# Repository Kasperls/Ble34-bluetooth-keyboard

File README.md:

# Ble34-bluetooth-keyboard
Files from the Ble34 project

Custom PCB for a wireless keyboard using running ZMK on nRF52840.

Flashed using picoprobe as debugger.

The final keyboard has a slick case in mate black and can be used both wired and not.

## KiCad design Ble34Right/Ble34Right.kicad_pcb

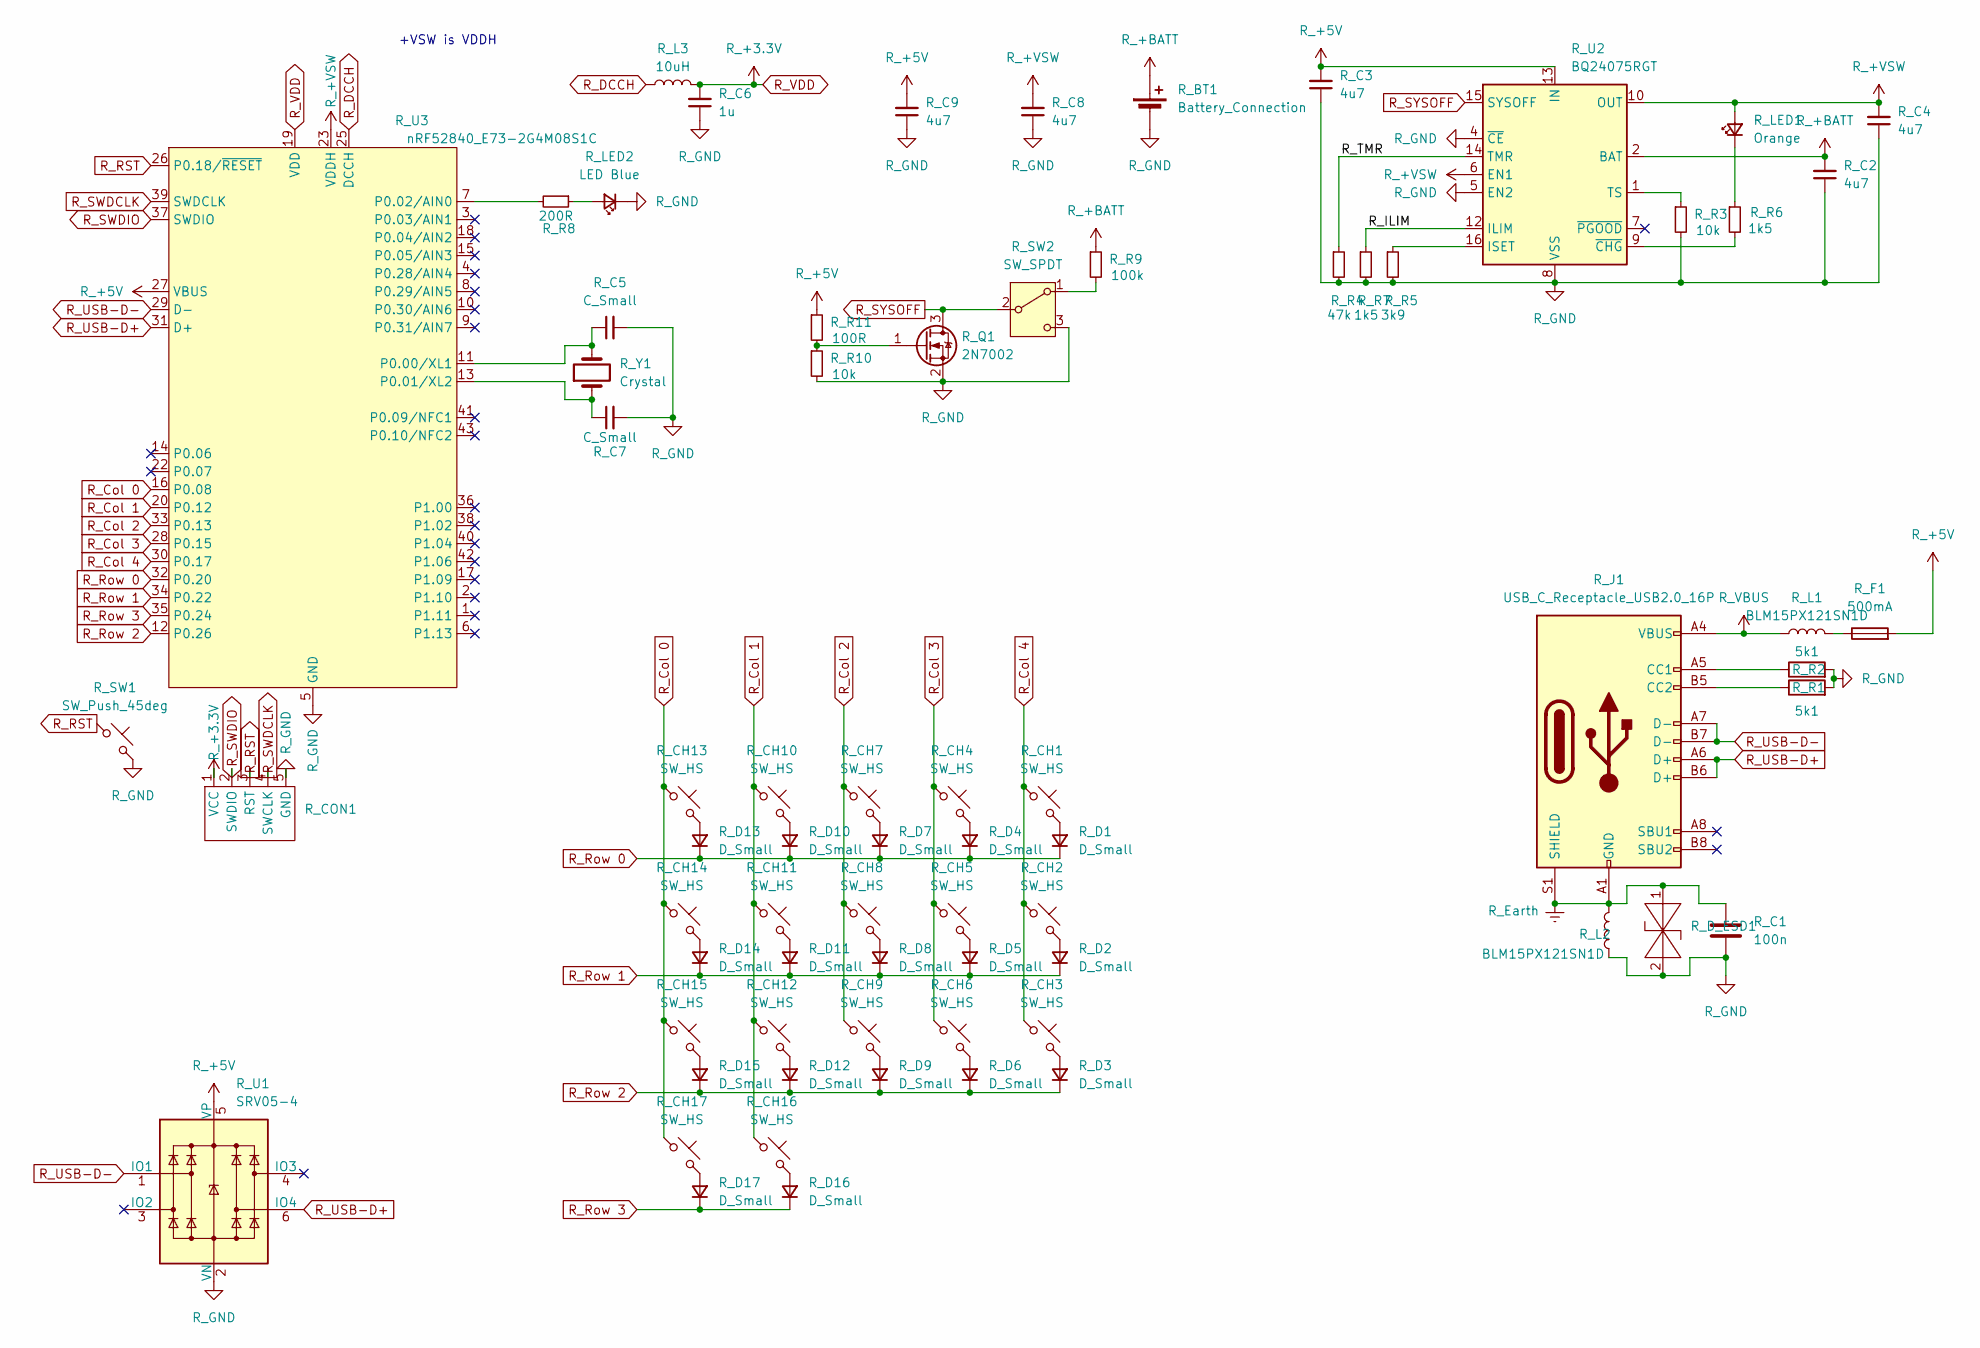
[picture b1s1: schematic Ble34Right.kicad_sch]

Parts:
R_BT1: Battery_Connection; Battery_Connector
R_C1: 100n; C_0603_1608Metric; LCSC C14663
R_C2, R_C3, R_C4, R_C8, R_C9: 4u7; C_0603_1608Metric; LCSC C1669
R_C5, R_C7: C_Small; C_0603_1608Metric; LCSC C38523
R_C6: 1u; C_0603_1608Metric; LCSC C115062
R_CH1, R_CH2, R_CH3, R_CH4, R_CH5, R_CH6, R_CH7, R_CH8, R_CH9, R_CH10, R_CH11, R_CH12, R_CH13, R_CH14, R_CH15, R_CH16, R_CH17: SW_HS; SW_choc_v1_HS_CPG135001S30_1u
R_CON1: SWD_CONNECTION
R_D1, R_D2, R_D3, R_D4, R_D5, R_D6, R_D7, R_D8, R_D9, R_D10, R_D11, R_D12, R_D13, R_D14, R_D15, R_D16, R_D17: D_Small; D_SOD-123; LCSC C2972760
R_D_ESD1: BSD3C051V; LCSC C151996
R_F1: 500mA; Fuse_0603_1608Metric; LCSC C910820
R_J1: USB_C_Receptacle_USB2.0_16P; USB_C_Receptacle_HRO_TYPE-C-31-M-14
R_L1, R_L2: BLM15PX121SN1D; R_0402_1005Metric; LCSC C88970
R_L3: 10uH; Fuse_0603_1608Metric; LCSC C1035
R_LED1: Orange; LED_0603_1608Metric; LCSC C2286
R_LED2: LED Blue; LED_0603_1608Metric; LCSC C2288
R_Q1: 2N7002; SOT-23; LCSC C332103
R_R1, R_R2: 5k1; R_0603_1608Metric; LCSC C23186
R_R3, R_R10: 10k; R_0603_1608Metric; LCSC C2930027
R_R4: 47k; R_0603_1608Metric; LCSC C2907042
R_R5: 3k9; R_0603_1608Metric; LCSC C2924132
R_R6, R_R7: 1k5; R_0603_1608Metric; LCSC C22843
R_R8: 200R; R_0603_1608Metric; LCSC C8218
R_R9: 100k; R_0603_1608Metric; LCSC C14675
R_R11: 100R; R_0603_1608Metric; LCSC C22775
R_SW1: SW_Push_45deg; TS-1088-SW; LCSC C720477
R_SW2: SW_SPDT; SW_MSK12C02-HB; LCSC C963206
R_U1: SRV05-4; SOT-23-6; LCSC C558418
R_U2: BQ24075RGT; VQFN-16-1EP_3x3mm_P0.5mm_EP1.6x1.6mm; LCSC C2865459
R_U3: nRF52840_E73-2G4M08S1C; LCSC C356849
R_Y1: Crystal; Crystal_SMD_3215-2Pin_3.2x1.5mm; LCSC C97606

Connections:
/R_ILIM: R_R7.1, R_U2.12 (ILIM)
/R_TMR: R_R4.1, R_U2.14 (TMR)
unnamed: R_CH13.2, R_D13.2 (A)
unnamed: R_CH10.2, R_D10.2 (A)
unnamed: R_CH7.2, R_D7.2 (A)
unnamed: R_CH4.2, R_D4.2 (A)
unnamed: R_CH1.2, R_D1.2 (A)
unnamed: R_CH14.2, R_D14.2 (A)
unnamed: R_CH11.2, R_D11.2 (A)
unnamed: R_CH8.2, R_D8.2 (A)
unnamed: R_CH5.2, R_D5.2 (A)
unnamed: R_CH2.2, R_D2.2 (A)
unnamed: R_CH15.2, R_D15.2 (A)
unnamed: R_CH12.2, R_D12.2 (A)
unnamed: R_CH9.2, R_D9.2 (A)
unnamed: R_CH6.2, R_D6.2 (A)
unnamed: R_CH3.2, R_D3.2 (A)
unnamed: R_CH17.2, R_D17.2 (A)
unnamed: R_CH16.2, R_D16.2 (A)
unnamed: R_F1.1, R_L1.2
unnamed: R_J1.A5 (CC1), R_R2.1
unnamed: R_J1.B5 (CC2), R_R1.1
unnamed: R_LED1.1 (K), R_R6.1
unnamed: R_LED2.2 (A), R_R8.1
unnamed: R_Q1.1 (G), R_R10.1, R_R11.2
unnamed: R_R9.2, R_SW2.1 (A)
unnamed: R_C5.1, R_U3.11 (P0.00/XL1), R_Y1.2
unnamed: R_C7.1, R_U3.13 (P0.01/XL2), R_Y1.1
unnamed: R_R8.2, R_U3.7 (P0.02/AIN0)
unnamed: R_R5.1, R_U2.16 (ISET)
unnamed: R_R3.1, R_U2.1 (TS)
unnamed: R_R6.2, R_U2.9 (~CHG)
R_+5V: R_C3.2, R_C9.2, R_F1.2, R_R11.1, R_U1.5 (VP), R_U2.13 (IN), R_U3.27 (VBUS)
R_+BATT: R_BT1.1 (+), R_C2.2, R_R9.1, R_U2.2 (BAT), R_U2.3 (BAT)
R_+VSW: R_C4.2, R_C8.2, R_LED1.2 (A), R_U2.6 (EN1), R_U2.10 (OUT), R_U2.11 (OUT), R_U3.23 (VDDH)
R_Col 0: R_CH13.1, R_CH14.1, R_CH15.1, R_CH17.1, R_U3.16 (P0.08)
R_Col 1: R_CH10.1, R_CH11.1, R_CH12.1, R_CH16.1, R_U3.20 (P0.12)
R_Col 2: R_CH7.1, R_CH8.1, R_CH9.1, R_U3.33 (P0.13)
R_Col 3: R_CH4.1, R_CH5.1, R_CH6.1, R_U3.28 (P0.15)
R_Col 4: R_CH1.1, R_CH2.1, R_CH3.1, R_U3.30 (P0.17)
R_DCCH: R_L3.1, R_U3.25 (DCCH)
R_Earth: R_C1.1, R_D_ESD1.1, R_J1.A1 (GND), R_J1.A12 (GND), R_J1.B1 (GND), R_J1.B12 (GND), R_J1.S1 (SHIELD), R_L2.2
R_GND: R_BT1.2 (-), R_C1.2, R_C2.1, R_C3.1, R_C4.1, R_C5.2, R_C6.1, R_C7.2, R_C8.1, R_C9.1, R_CON1.5 (GND), R_D_ESD1.2, R_L2.1, R_LED2.1 (K), R_Q1.2 (S), R_R1.2, R_R2.2, R_R3.2, R_R4.2, R_R5.2, R_R7.2, R_R10.2, R_SW1.2, R_SW2.3 (C), R_U1.2 (VN), R_U2.4 (~CE), R_U2.5 (EN2), R_U2.8 (VSS), R_U2.17 (VSS), R_U3.5 (GND), R_U3.21 (GND), R_U3.24 (GND)
R_RST: R_CON1.3 (RST), R_SW1.1, R_U3.26 (P0.18/~RESET)
R_Row 0: R_D1.1 (K), R_D4.1 (K), R_D7.1 (K), R_D10.1 (K), R_D13.1 (K), R_U3.32 (P0.20)
R_Row 1: R_D2.1 (K), R_D5.1 (K), R_D8.1 (K), R_D11.1 (K), R_D14.1 (K), R_U3.34 (P0.22)
R_Row 2: R_D3.1 (K), R_D6.1 (K), R_D9.1 (K), R_D12.1 (K), R_D15.1 (K), R_U3.12 (P0.26)
R_Row 3: R_D16.1 (K), R_D17.1 (K), R_U3.35 (P0.24)
R_SWDCLK: R_CON1.4 (SWCLK), R_U3.39 (SWDCLK)
R_SWDIO: R_CON1.2 (SWDIO), R_U3.37 (SWDIO)
R_SYSOFF: R_Q1.3 (D), R_SW2.2 (B), R_U2.15 (SYSOFF)
R_USB-D+: R_J1.A6 (D+), R_J1.B6 (D+), R_U1.6 (IO4), R_U3.31 (D+)
R_USB-D-: R_J1.A7 (D-), R_J1.B7 (D-), R_U1.1 (IO1), R_U3.29 (D-)
R_VBUS: R_J1.A4 (VBUS), R_J1.A9 (VBUS), R_J1.B4 (VBUS), R_J1.B9 (VBUS), R_L1.1
R_VDD: R_C6.2, R_CON1.1 (VCC), R_L3.2, R_U3.19 (VDD)

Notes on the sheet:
+VSW is VDDH

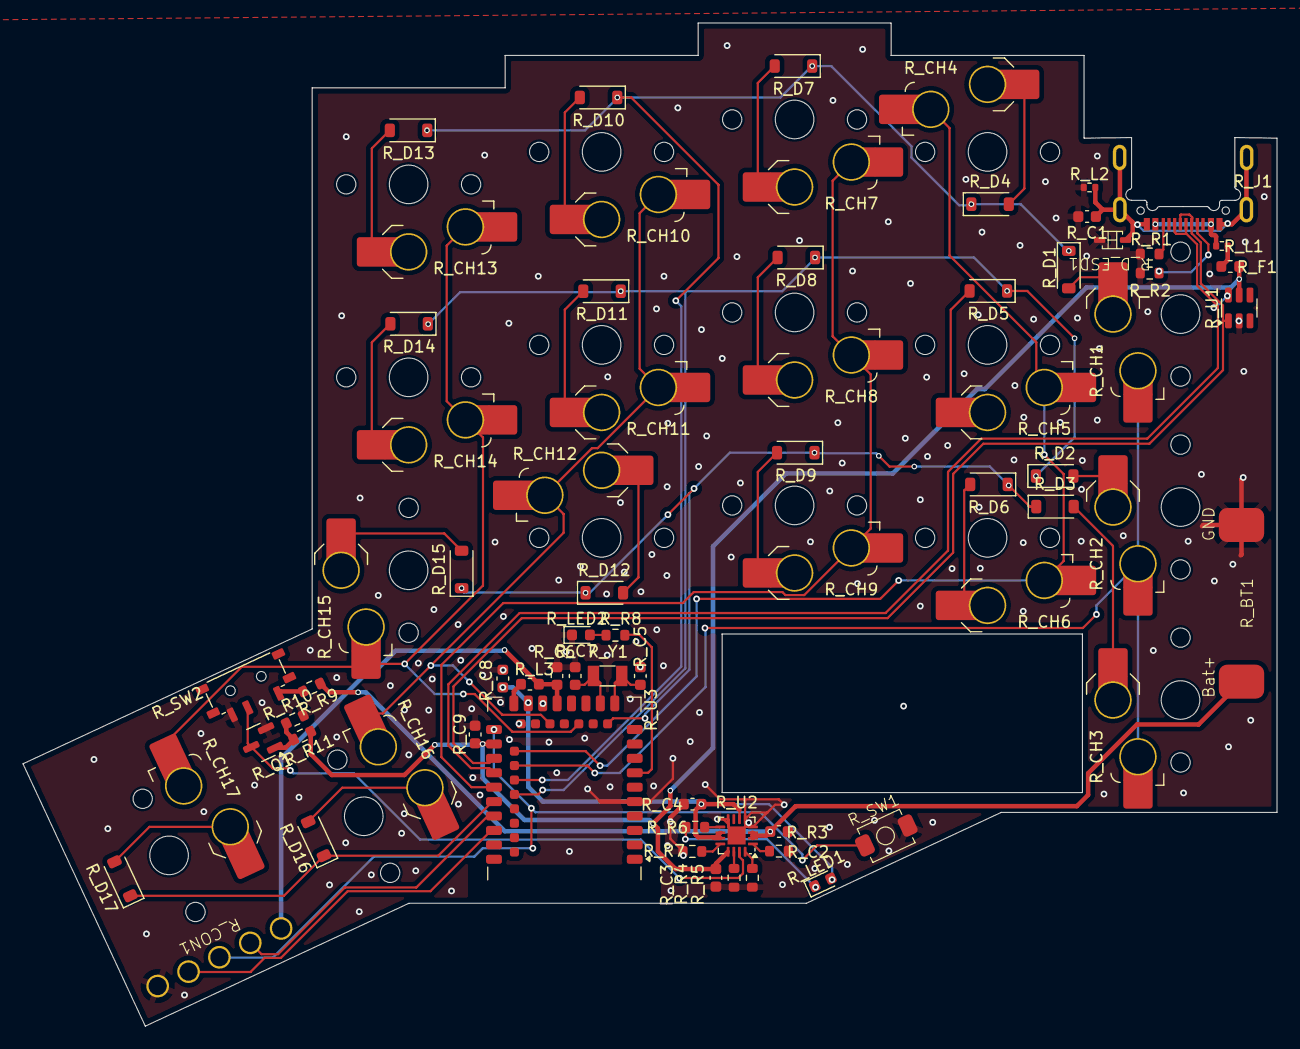
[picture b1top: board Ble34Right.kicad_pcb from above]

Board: 2 copper layers, 110.5 x 88.4 mm, 71 parts (0 on the bottom side), 55 nets.
